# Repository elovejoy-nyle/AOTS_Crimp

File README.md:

# AOTS_Crimp
Put crimp connectors on the AOTS Sensor using a custom PCB.
The perk here is the ability to have these made via a manufacturing vendor such as:
JLPCB or PCBWay, and have them arive ready to use.
<br><br>
<h1> Alternate due to parts availability...</h1>
https://www.digikey.com/en/models/2170998  
<br>
https://www.sensata.com/products/temperature/6700-series-220-subminiature-thermostat
<br><br>

<br><br>

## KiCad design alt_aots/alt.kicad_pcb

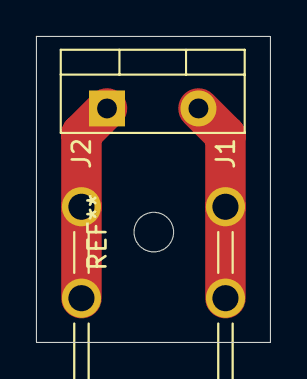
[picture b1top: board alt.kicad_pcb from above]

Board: 2 copper layers, 13.0 x 17.0 mm, 3 parts (0 on the bottom side), 2 nets.

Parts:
D1: AOTS; TO-220-2_Vertical
J1, J2: 1217754-1; TE_1217754-1

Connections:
unnamed: D1.2 (A), J1.1_1 (1), J1.1_2 (1__1)
unnamed: D1.1 (K), J2.1_1 (1), J2.1_2 (1__1)

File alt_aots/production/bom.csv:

Designator,Footprint,Quantity,Value,LCSC Part #
D1,TO-220-2_Vertical,1,AOTS,C17325979
"J1, J2",TE_1217754-1,2,1217754-1,C305825

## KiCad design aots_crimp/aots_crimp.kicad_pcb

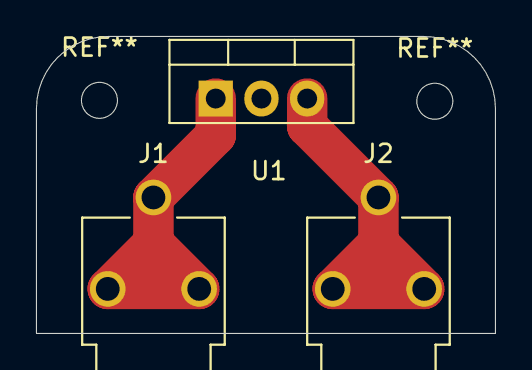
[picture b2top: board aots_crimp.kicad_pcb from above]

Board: 2 copper layers, 25.5 x 16.5 mm, 3 parts (0 on the bottom side), 2 nets.

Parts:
J1, J2: 4910; KEYSTONE_4910
U1: AOTS; TO-220-3_Vertical

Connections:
unnamed: J1.1_1, J1.1_2, J1.1_3, U1.1 (ADJ)
unnamed: J2.1_1, J2.1_2, J2.1_3, U1.3 (VI)

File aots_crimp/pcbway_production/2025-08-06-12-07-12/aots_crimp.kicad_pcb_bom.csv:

Designator,Quantity,Value,Footprint,Package,MPN,DNP,Mount_Type,PARTREV,SNAPEDA_PN,STANDARD,MAXIMUM_PACKAGE_HEIGHT,MANUFACTURER,LCSC,Description
"J1, J2",2,4910,KEYSTONE_4910,,,,tht,C,4910,Manufacturer Recommendations,4.24mm,Keystone,C3029546,
U1,1,AOTS,TO-220-3_Vertical,,,,tht,,,,,,C17325979,"1.5A 35V Adjustable Linear Regulator, TO-220"

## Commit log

2025-08-06 found LCSC parts, Generate BOM
2025-08-06 gerbers
2025-08-08 alternate due to parts available.
2025-08-08 production parts
